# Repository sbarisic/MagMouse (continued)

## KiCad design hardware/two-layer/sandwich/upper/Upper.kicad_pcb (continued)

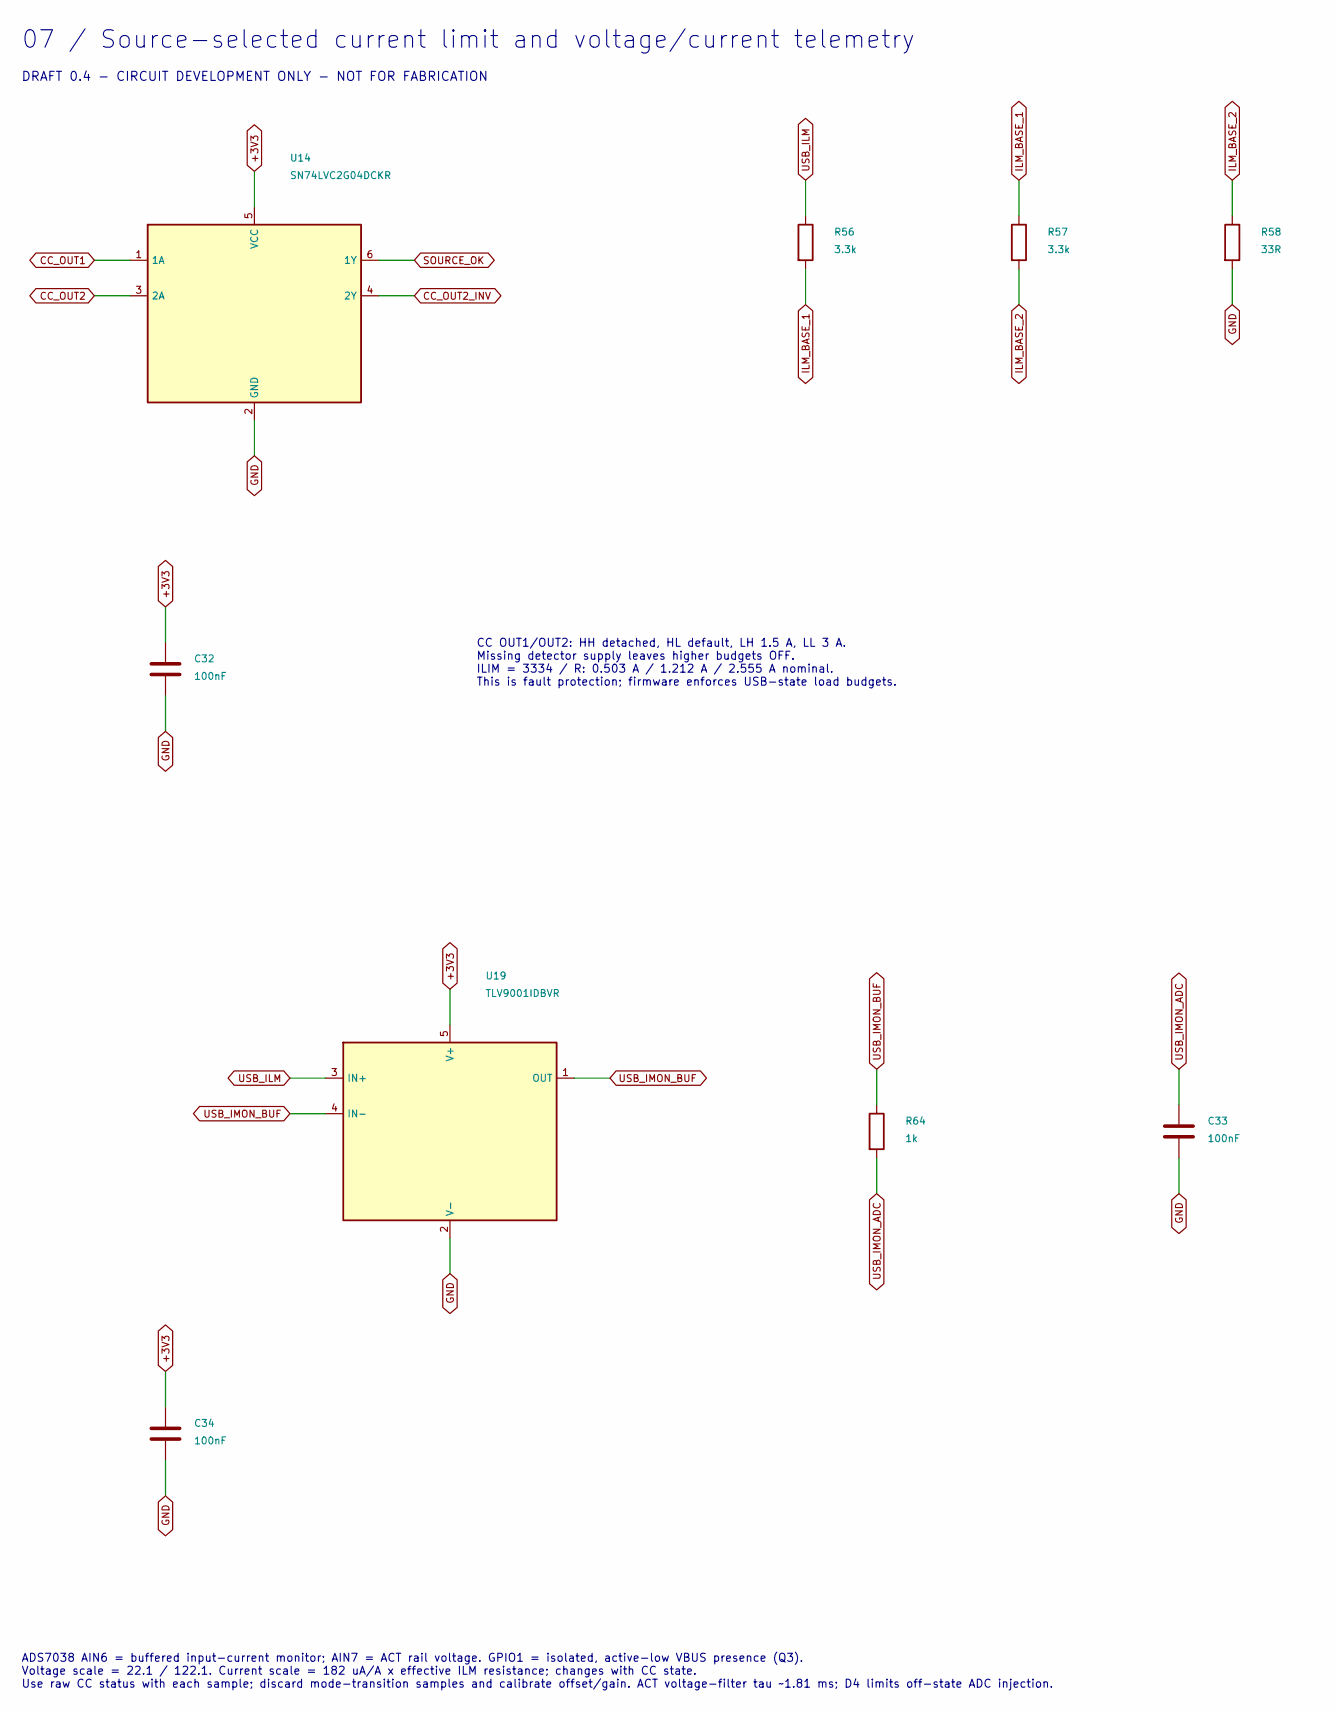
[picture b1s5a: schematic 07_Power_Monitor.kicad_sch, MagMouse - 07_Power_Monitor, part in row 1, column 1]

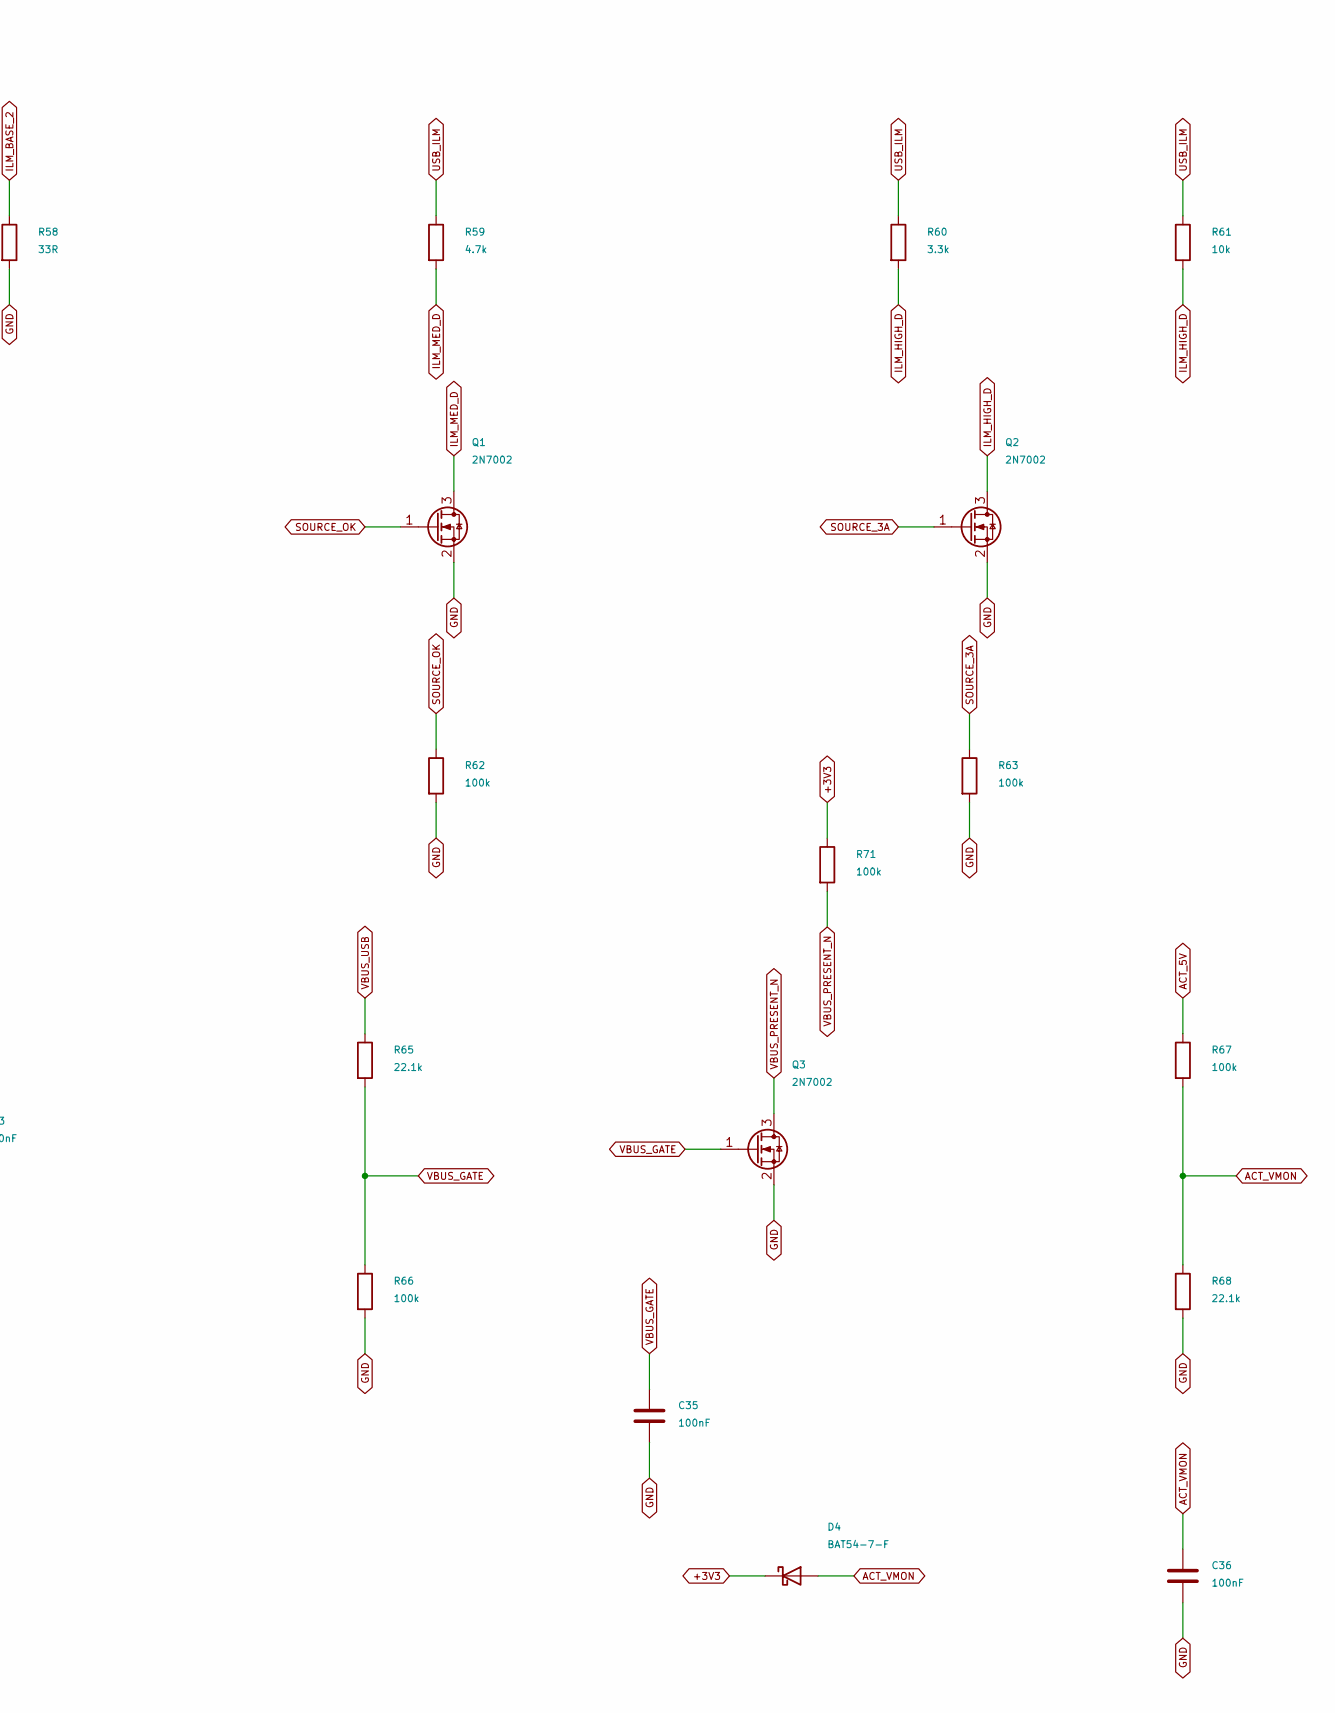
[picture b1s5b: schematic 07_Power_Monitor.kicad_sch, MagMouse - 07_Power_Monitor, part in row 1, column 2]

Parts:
C32, C33, C34, C35, C36: 100nF; C_1206_3216Metric; Rating 50 V, X7R, 10%; MPN CC1206KRX7R9BB104
D4: BAT54-7-F; SOT-23; MPN BAT54-7-F; LCSC C106920
Q1, Q2, Q3: 2N7002; SOT-23; MPN 2N7002; LCSC C8545
R56, R57, R60: 3.3k; R_1206_3216Metric; Rating 0.25 W, 1%; MPN RC1206FR-073K3L
R58: 33R; R_1206_3216Metric; Rating 0.25 W, 1%; MPN RC1206FR-0733RL
R59: 4.7k; R_1206_3216Metric; Rating 0.25 W, 1%; MPN RC1206FR-074K7L
R61: 10k; R_1206_3216Metric; Rating 0.25 W, 1%; MPN RC1206FR-0710KL
R62, R63, R66, R67, R71: 100k; R_1206_3216Metric; Rating 0.25 W, 1%; MPN RC1206FR-07100KL
R64: 1k; R_1206_3216Metric; Rating 0.25 W, 1%; MPN RC1206FR-071KL
R65, R68: 22.1k; R_1206_3216Metric; Rating 0.25 W, 1%; MPN RC1206FR-0722K1L
U14: SN74LVC2G04DCKR; SOT-363_SC-70-6; MPN SN74LVC2G04DCKR; LCSC C105251
U19: TLV9001IDBVR; SOT-23-5; MPN TLV9001IDBVR; LCSC C398363

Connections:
+3V3: C32.1, C34.1, D4.3 (K), R71.1, U14.5 (VCC), U19.5 (V+); also elsewhere on the board
ACT_5V: R67.1; also elsewhere on the board
ACT_VMON: C36.1, D4.1 (A), R67.2, R68.1; also elsewhere on the board
CC_OUT1: U14.1 (1A); also elsewhere on the board
CC_OUT2: U14.3 (2A); also elsewhere on the board
CC_OUT2_INV: U14.4 (2Y); also elsewhere on the board
GND: C32.2, C33.2, C34.2, C35.2, C36.2, Q1.2 (S), Q2.2 (S), Q3.2 (S), R58.2, R62.2, R63.2, R66.2, R68.2, U14.2 (GND), U19.2 (V-); also elsewhere on the board
ILM_BASE_1: R56.2, R57.1
ILM_BASE_2: R57.2, R58.1
ILM_HIGH_D: Q2.3 (D), R60.2, R61.2
ILM_MED_D: Q1.3 (D), R59.2
SOURCE_3A: Q2.1 (G), R63.1; also elsewhere on the board
SOURCE_OK: Q1.1 (G), R62.1, U14.6 (1Y); also elsewhere on the board
USB_ILM: R56.1, R59.1, R60.1, R61.1, U19.3 (IN+); also elsewhere on the board
USB_IMON_ADC: C33.1, R64.2; also elsewhere on the board
USB_IMON_BUF: R64.1, U19.1 (OUT), U19.4 (IN-)
VBUS_GATE: C35.1, Q3.1 (G), R65.2, R66.1
VBUS_PRESENT_N: Q3.3 (D), R71.2; also elsewhere on the board
VBUS_USB: R65.1; also elsewhere on the board

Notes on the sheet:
07 / Source-selected current limit and voltage/current telemetry
DRAFT 0.4 - CIRCUIT DEVELOPMENT ONLY - NOT FOR FABRICATION
CC OUT1/OUT2: HH detached, HL default, LH 1.5 A, LL 3 A. Missing detector supply leaves higher budgets OFF. ILIM = 3334 / R: 0.503 A / 1.212 A / 2.555 A nominal. This is fault protection; firmware enforces USB-state load budgets.
ADS7038 AIN6 = buffered input-current monitor; AIN7 = ACT rail voltage. GPIO1 = isolated, active-low VBUS presence (Q3). Voltage scale = 22.1 / 122.1. Current scale = 182 uA/A x effective ILM resistance; changes with CC state. Use raw CC status with each sample; discard mode-transition samples and 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

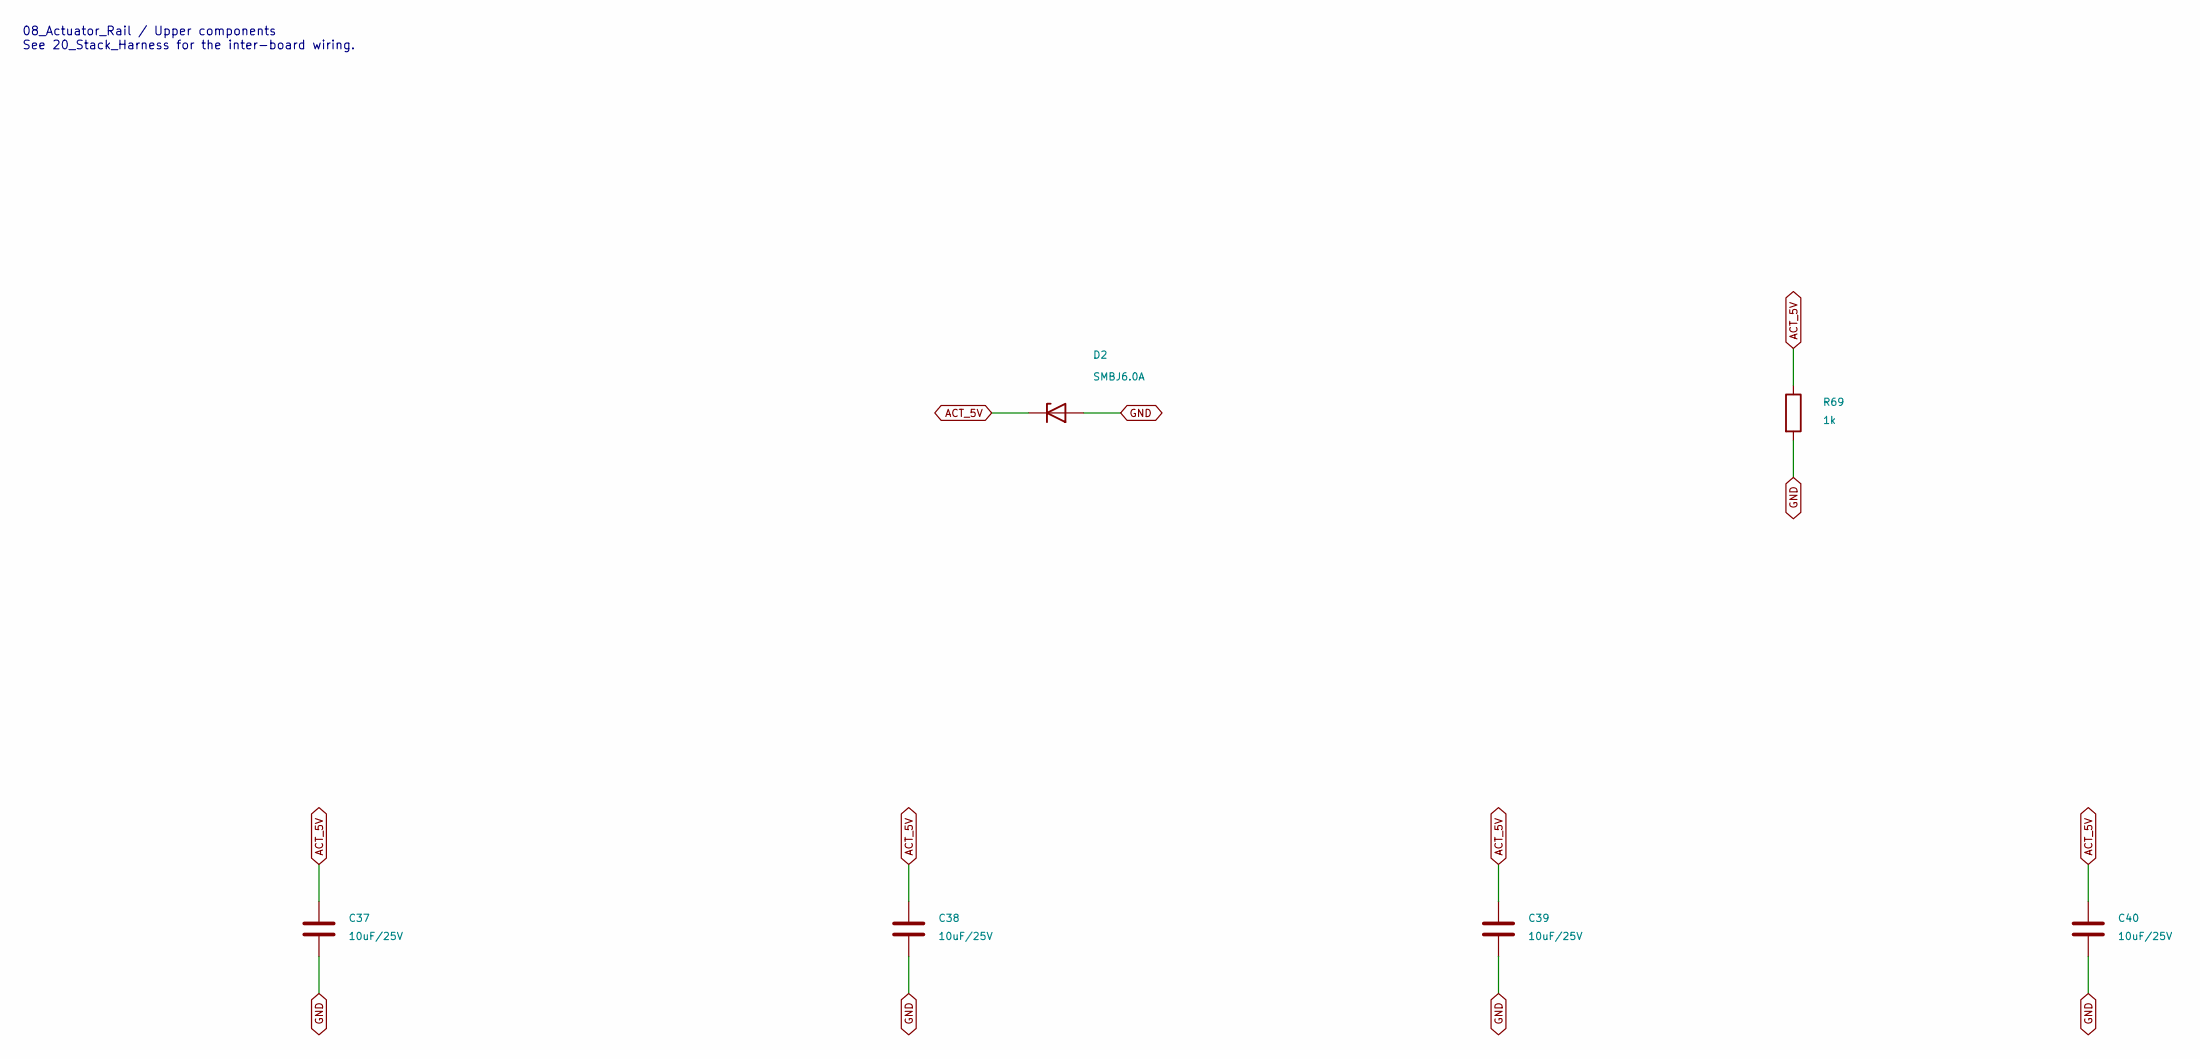
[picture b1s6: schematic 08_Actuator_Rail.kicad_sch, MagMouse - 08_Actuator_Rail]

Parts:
C37, C38, C39, C40: 10uF/25V; C_1206_3216Metric; Rating 25 V, X5R, 10%; MPN CL31A106KAHNNNE
D2: SMBJ6.0A; D_SMB; MPN SMBJ6.0A; LCSC C83270
R69: 1k; R_1206_3216Metric; Rating 0.25 W, 1%; MPN RC1206FR-071KL

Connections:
ACT_5V: C37.1, C38.1, C39.1, C40.1, D2.1 (K), R69.1; also elsewhere on the board
GND: C37.2, C38.2, C39.2, C40.2, D2.2 (A), R69.2; also elsewhere on the board

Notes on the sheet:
08_Actuator_Rail / Upper components See 20_Stack_Harness for the inter-board wiring.

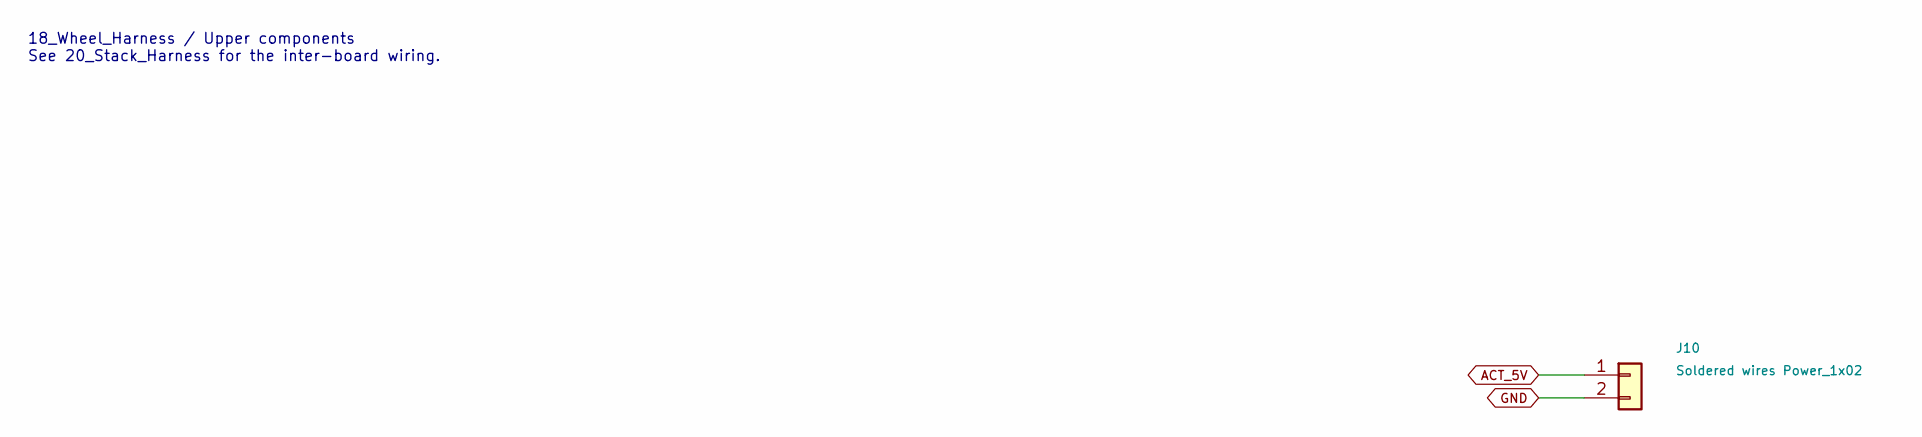
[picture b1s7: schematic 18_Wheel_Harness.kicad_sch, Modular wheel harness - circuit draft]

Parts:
J10: Soldered wires Power_1x02; Wire_Power_1x02_P2.54mm

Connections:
ACT_5V: J10.1; also elsewhere on the board
GND: J10.2; also elsewhere on the board

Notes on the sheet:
18_Wheel_Harness / Upper components See 20_Stack_Harness for the inter-board wiring.

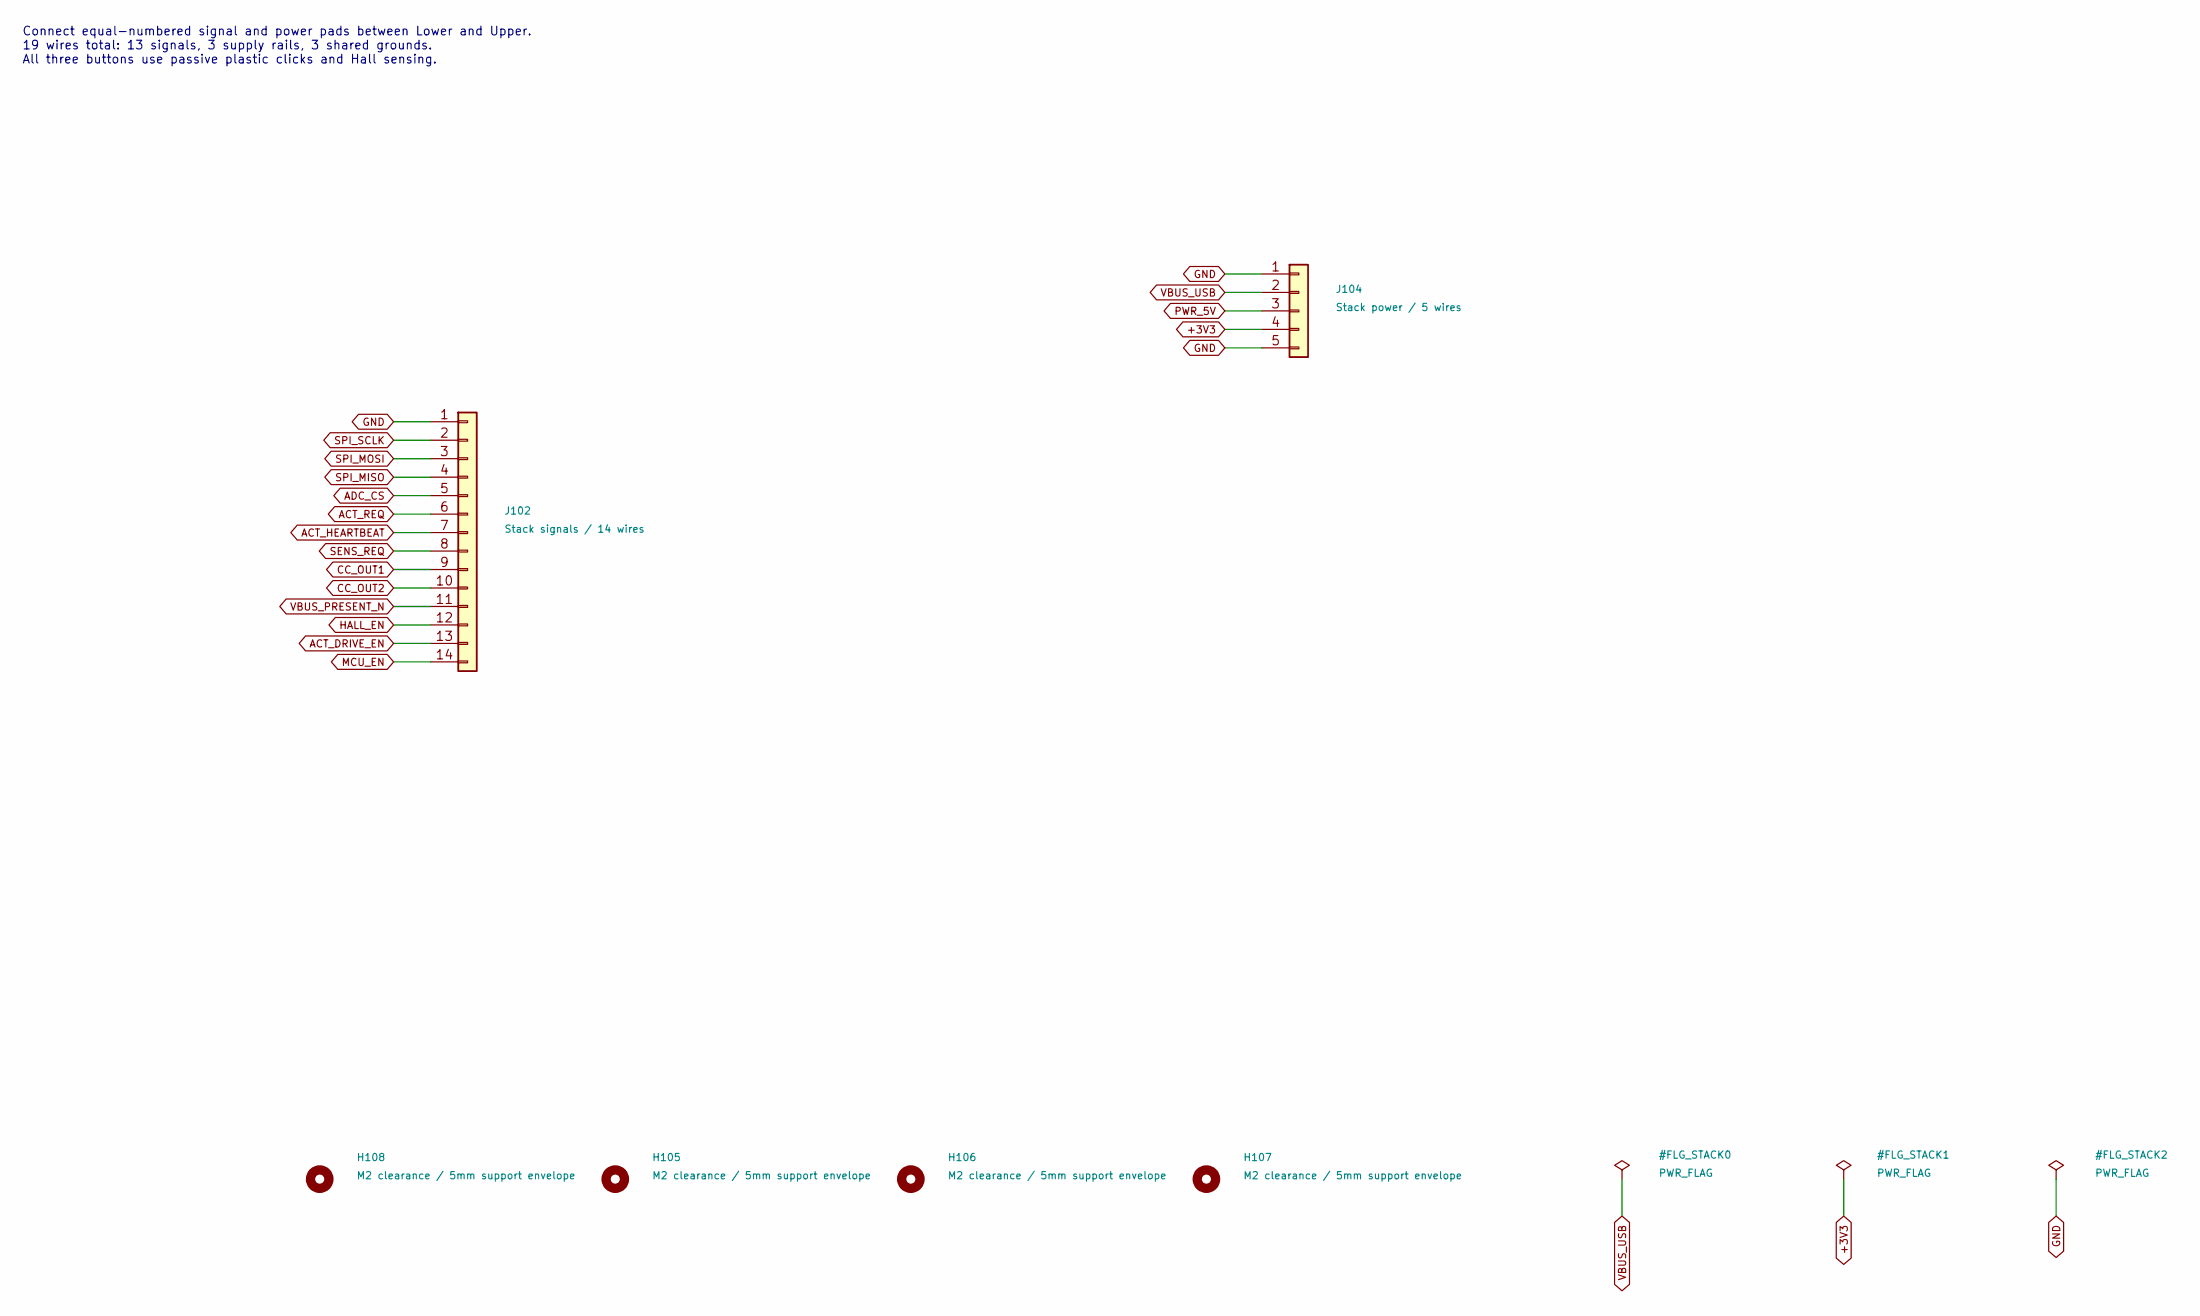
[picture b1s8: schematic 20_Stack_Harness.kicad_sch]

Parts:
H105, H106, H107, H108: M2 clearance / 5mm support envelope; MountingHole_2.2mm_M2_5mm_Envelope
J102: Stack signals / 14 wires; Wire_Stack_Signal_14
J104: Stack power / 5 wires; Wire_Stack_Power_5

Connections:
+3V3: J104.4; also elsewhere on the board
ACT_DRIVE_EN: J102.13; also elsewhere on the board
ACT_HEARTBEAT: J102.7; also elsewhere on the board
ACT_REQ: J102.6; also elsewhere on the board
ADC_CS: J102.5; also elsewhere on the board
CC_OUT1: J102.9; also elsewhere on the board
CC_OUT2: J102.10; also elsewhere on the board
GND: J102.1, J104.1, J104.5; also elsewhere on the board
HALL_EN: J102.12; also elsewhere on the board
MCU_EN: J102.14; also elsewhere on the board
PWR_5V: J104.3; also elsewhere on the board
SENS_REQ: J102.8; also elsewhere on the board
SPI_MISO: J102.4; also elsewhere on the board
SPI_MOSI: J102.3; also elsewhere on the board
SPI_SCLK: J102.2; also elsewhere on the board
VBUS_PRESENT_N: J102.11; also elsewhere on the board
VBUS_USB: J104.2; also elsewhere on the board

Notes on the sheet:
Connect equal-numbered signal and power pads between Lower and Upper. 19 wires total: 13 signals, 3 supply rails, 3 shared grounds. All three buttons use passive plastic clicks and Hall sensing.

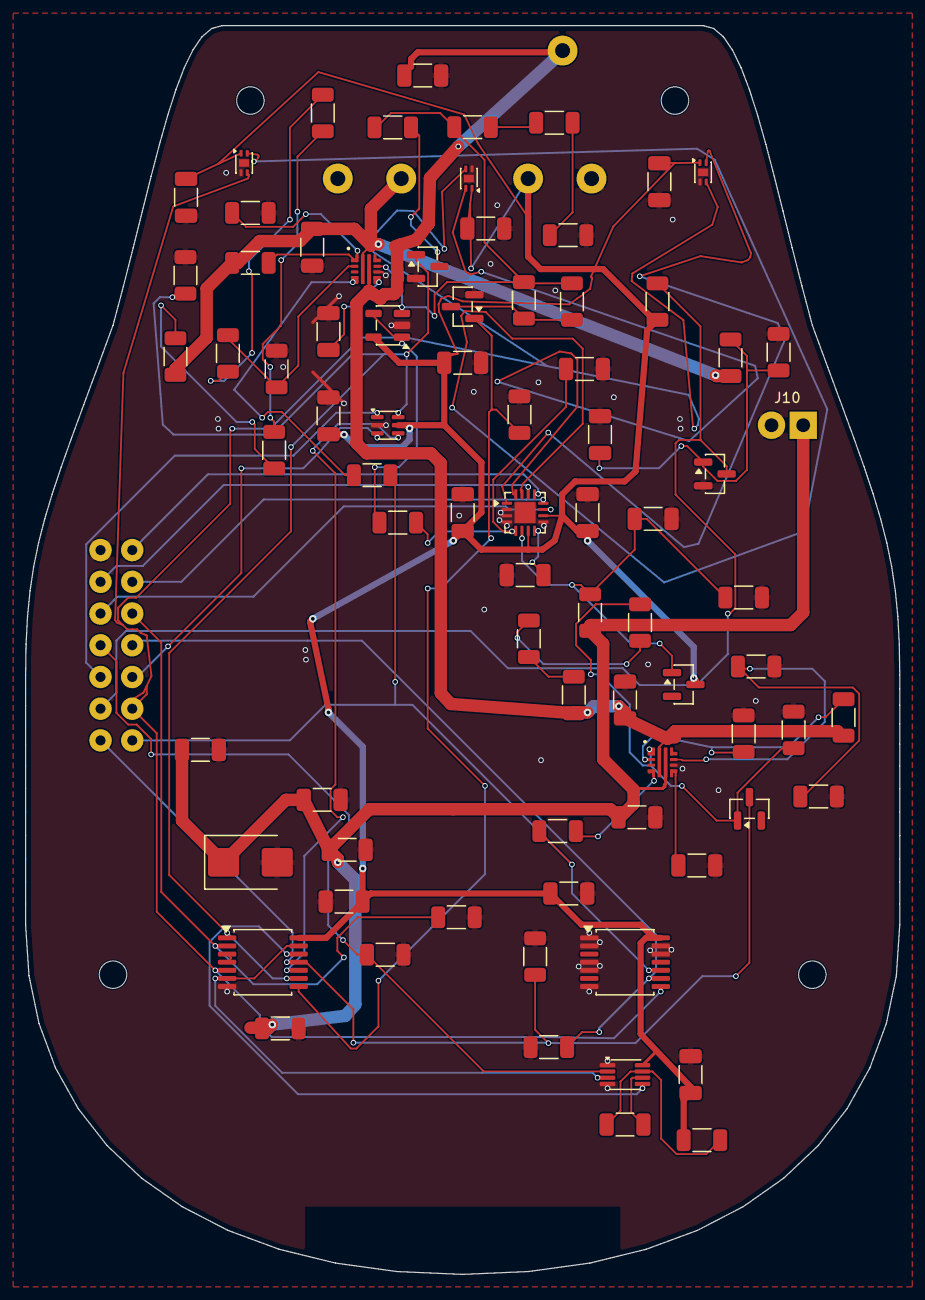
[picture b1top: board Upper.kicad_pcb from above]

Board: 2 copper layers, 70.0 x 100.0 mm, 85 parts (0 on the bottom side), 53 nets.

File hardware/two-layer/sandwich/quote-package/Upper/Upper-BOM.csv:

Comment,Designator,Footprint,LCSC Part #,Manufacturer,MPN,Quantity
100nF,"C16,C17,C18,C28,C29,C31,C32,C33,C34,C35,C36",C_1206_3216Metric,,YAGEO,CC1206KRX7R9BB104,11
1uF/50V,"C19,C20,C21,C24,C27,C89",C_1206_3216Metric,,Samsung Electro-Mechanics,CL31B105KBHNNNE,6
10nF,"C25,C26",C_1206_3216Metric,,YAGEO,CC1206KRX7R9BB103,2
10uF/25V,"C37,C38,C39,C40,C88",C_1206_3216Metric,,Samsung Electro-Mechanics,CL31A106KAHNNNE,5
SMBJ6.0A,D2,D_SMB,C83270,Littelfuse,SMBJ6.0A,1
BAT54-7-F,"D3,D4",SOT-23,C106920,Diodes Incorporated,BAT54-7-F,2
2N7002,"Q1,Q2,Q3",SOT-23,C8545,Jiangsu Changjing Electronics Technology,2N7002,3
22.1k,"R29,R41,R65,R68",R_1206_3216Metric,,YAGEO,RC1206FR-0722K1L,4
10k,"R30,R36,R37,R38,R46,R47,R48,R49,R61,R70",R_1206_3216Metric,,YAGEO,RC1206FR-0710KL,10
100k,"R31,R32,R33,R34,R35,R40,R62,R63,R66,R67,R71",R_1206_3216Metric,,YAGEO,RC1206FR-07100KL,11
11k,R39,R_1206_3216Metric,,YAGEO,RC1206FR-0711KL,1
3.3k,"R42,R43,R56,R57,R60",R_1206_3216Metric,,YAGEO,RC1206FR-073K3L,5
1k,"R44,R45,R64,R69",R_1206_3216Metric,,YAGEO,RC1206FR-071KL,4
33R,R58,R_1206_3216Metric,,YAGEO,RC1206FR-0733RL,1
4.7k,R59,R_1206_3216Metric,,YAGEO,RC1206FR-074K7L,1
ADS7038IRTER,U10,WQFN-16-1EP_3x3mm_P0.5mm_EP1.68x1.68mm,C2871580,Texas Instruments,ADS7038IRTER,1
TPS259470LRPWR,"U12,U13",Texas_RPW0010A,C3662793,Texas Instruments,TPS259470LRPWR,2
SN74LVC2G04DCKR,U14,SOT-363_SC-70-6,C105251,Texas Instruments,SN74LVC2G04DCKR,1
SN74LVC1G123DCUR,U15,VSSOP-8_2.3x2mm_P0.5mm,C352969,Texas Instruments,SN74LVC1G123DCUR,1
SN74LVC08APWR,"U16,U18",TSSOP-14_4.4x5mm_P0.65mm,C465737,Texas Instruments,SN74LVC08APWR,2
TLV9001IDBVR,U19,SOT-23-5,C398363,Texas Instruments,TLV9001IDBVR,1
TMAG5253BA2IQDMRR,"U7,U8,U9",Texas_X2SON-4-1EP_1.1x1.4mm_P0.5mm_EP0.8x0.6mm,C35414983,Texas Instruments,TMAG5253BA2IQDMRR,3

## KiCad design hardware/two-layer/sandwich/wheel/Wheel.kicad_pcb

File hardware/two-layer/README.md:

# Active two-layer PCBs

Open the [stacked-board project overview](sandwich/README.md).

| Board | Project | Outline |
|---|---|---|
| Lower Main | [Lower](sandwich/lower/Lower.kicad_pro) | 70 x 100 mm tapered |
| Upper Main | [Upper](sandwich/upper/Upper.kicad_pro) | 70 x 100 mm tapered |
| Wheel | [Wheel](sandwich/wheel/Wheel.kicad_pro) | 70 x 67 mm clipped Main profile |

The `sandwich` directory contains the active routing tools, review evidence,
3D exports, current quote packages and three-board panel. `main-circuit` is the
combined schematic reference used to check the Lower/Upper partition; edit the
independent board schematics for development. Shared resources are in
[hardware/common](../common/README.md).

The oversized two-layer experiments and their one-time conversion scripts have
been removed from this checkout. They remain in [Git history](../../docs/history/README.md).

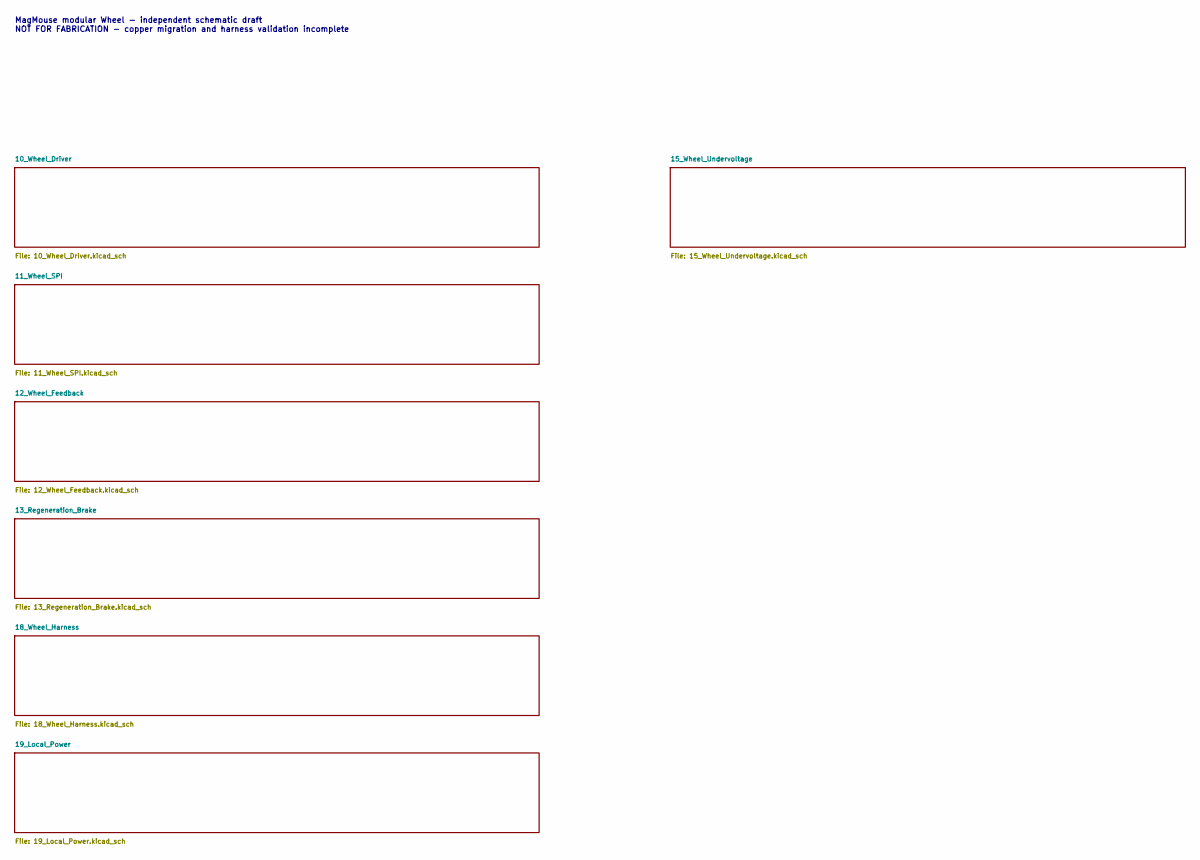
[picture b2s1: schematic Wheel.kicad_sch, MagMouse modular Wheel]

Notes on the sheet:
MagMouse modular Wheel - independent schematic draft NOT FOR FABRICATION - copper migration and harness validation incomplete
